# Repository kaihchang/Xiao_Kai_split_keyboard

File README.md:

[still in design process]

After using my previous Ascend design for weeks, I decided that MX switches are too "big" (height is okay) and wanted a Choc kb that's different from my old Ferris Sweep.
This time I'd like to give Xiao BLE a try and my experience with Oled displays wasn't great (power-drawing and not really useful except for debugging), neither was a fan for splays (occupies space without really adding much to the "ergonomics"), so this time I'll go with a Sweep-ish variation with spreads that is customised for my hands.
Honestly encoders aren't really necessary since for me they're only useful for volume and bluetooth channel adjustments, but I've got 2 pins left and between encoder and TRRS socket for QMK to work, I chose former.

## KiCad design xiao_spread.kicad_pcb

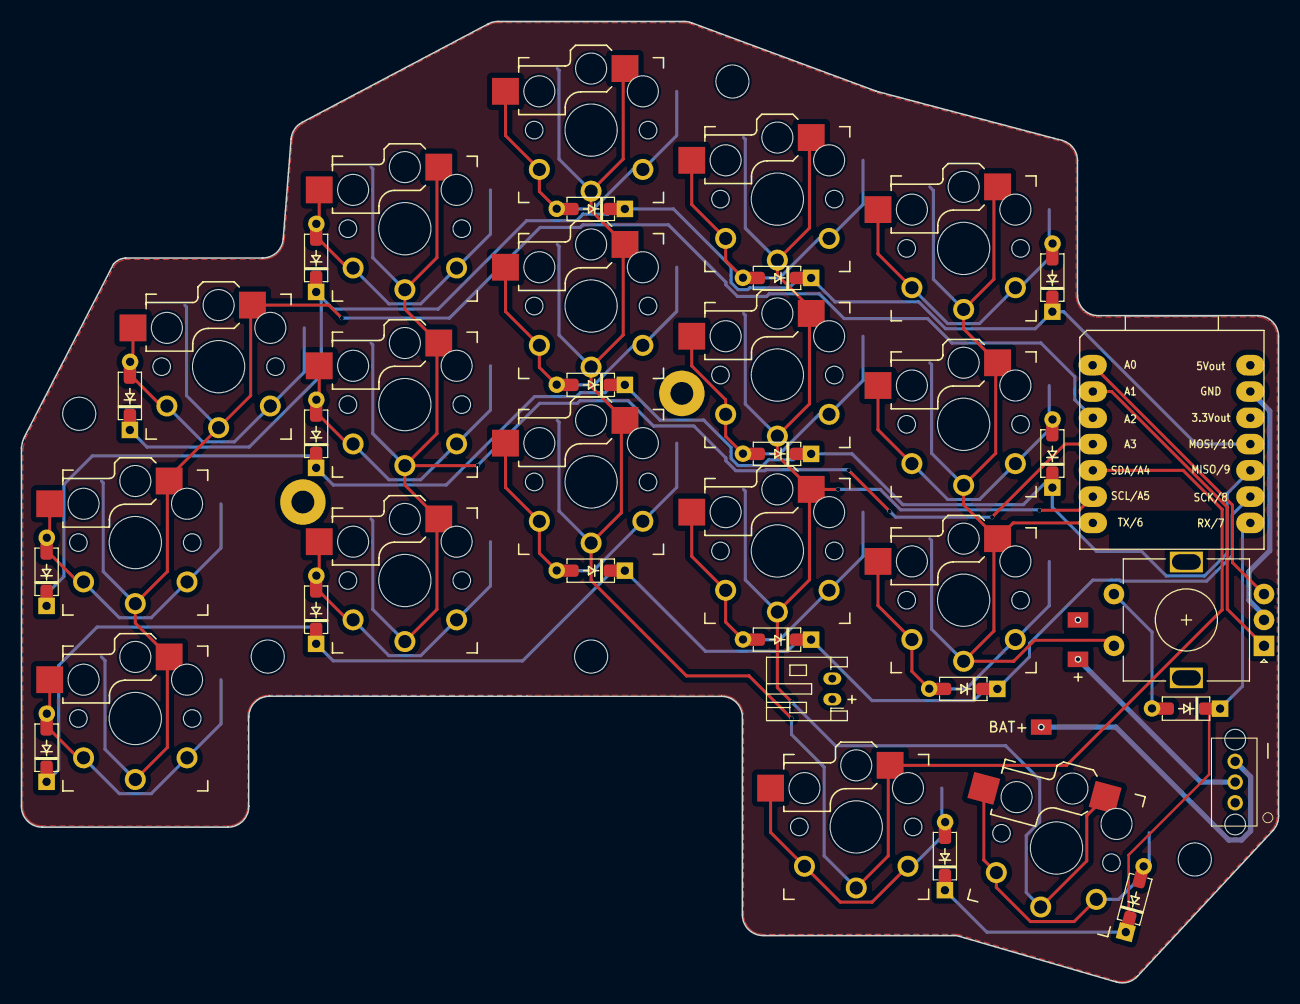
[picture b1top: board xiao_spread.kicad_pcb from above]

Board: 2 copper layers, 121.5 x 92.9 mm, 42 parts (0 on the bottom side), 32 nets.

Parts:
BT1: Battery_Cell; JST_PH_reversible
D1, D2, D3, D4, D5, D6, D7, D8, D9, D10, D11, D12, D13, D14, D15, D16, D17, D18: Diode; Compatible_diode_TH_SMD
J1: B5B-XH-A_LF__SN_; Switch_slide_TH_5P
JP1, JP2, JP3: Device_Jumper_NO_Small; link_pad
S1, S2, S3, S4, S5, S6, S7, S8, S9, S10, S11, S12, S13, S14, S15, S16, S17: Keyswitch; Kailh_socket_PG1350_optional_reversible
SW1: RotaryEncoder_Switch; RotaryEncoder_Alps_EC11E-Switch_Vertical_H20mm
U2: SeeeduinoXIAO; Xiao_nrf52840_BLE

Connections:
Col_0: S1.1, S6.1, S11.1, U2.2 (PA10_A2_D2)
Col_1: S2.1, S7.1, S12.1, U2.3 (PA11_A3_D3)
Col_2: S3.1, S8.1, S13.1, S16.1, U2.4 (PA8_A4_D4_SDA)
Col_3: S4.1, S9.1, S14.1, S17.1, U2.5 (PA9_A5_D5_SCL)
Col_4: S5.1, S10.1, S15.1, SW1.S2, U2.6 (PB08_A6_D6_TX)
EC_A: SW1.B, U2.0 (PA02_A0_D0)
EC_B: SW1.A, U2.1 (PA4_A1_D1)
GND: SW1.C, U2.12 (GND)
unnamed: D1.2 (A), S1.2
unnamed: D2.2 (A), S2.2
unnamed: D3.2 (A), S3.2
unnamed: D4.2 (A), S4.2
unnamed: D5.2 (A), S5.2
unnamed: D6.2 (A), S6.2
unnamed: D7.2 (A), S7.2
unnamed: D8.2 (A), S8.2
unnamed: D9.2 (A), S9.2
unnamed: D10.2 (A), S10.2
unnamed: D11.2 (A), S11.2
unnamed: D12.2 (A), S12.2
unnamed: D13.2 (A), S13.2
unnamed: D14.2 (A), S14.2
unnamed: D15.2 (A), S15.2
unnamed: D16.2 (A), S16.2
unnamed: D17.2 (A), S17.2
unnamed: D18.2 (A), SW1.S1
unnamed: J1.3, JP1.1
unnamed: J1.4, JP3.1
Row_0: D1.1 (K), D2.1 (K), D3.1 (K), D4.1 (K), D5.1 (K), U2.10 (PA6_A10_D10_MOSI)
Row_1: D6.1 (K), D7.1 (K), D8.1 (K), D9.1 (K), D10.1 (K), U2.9 (PA5_A9_D9_MISO)
Row_2: D11.1 (K), D12.1 (K), D13.1 (K), D14.1 (K), D15.1 (K), U2.8 (PA7_A8_D8_SCK)
Row_3: D16.1 (K), D17.1 (K), D18.1 (K), U2.7 (PB09_A7_D7_RX)

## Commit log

2024-03-15 user update
